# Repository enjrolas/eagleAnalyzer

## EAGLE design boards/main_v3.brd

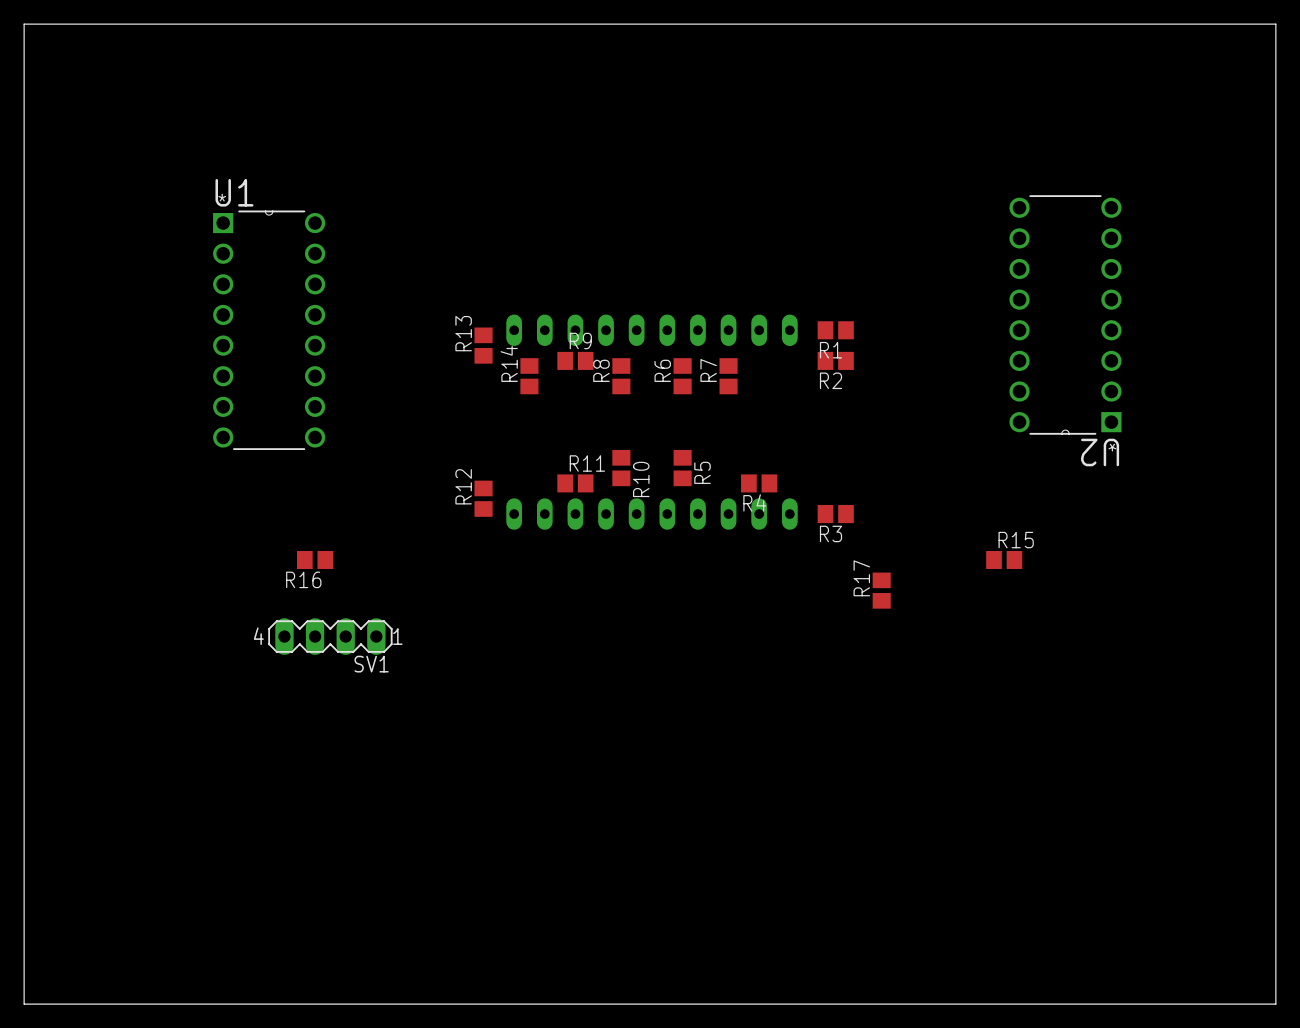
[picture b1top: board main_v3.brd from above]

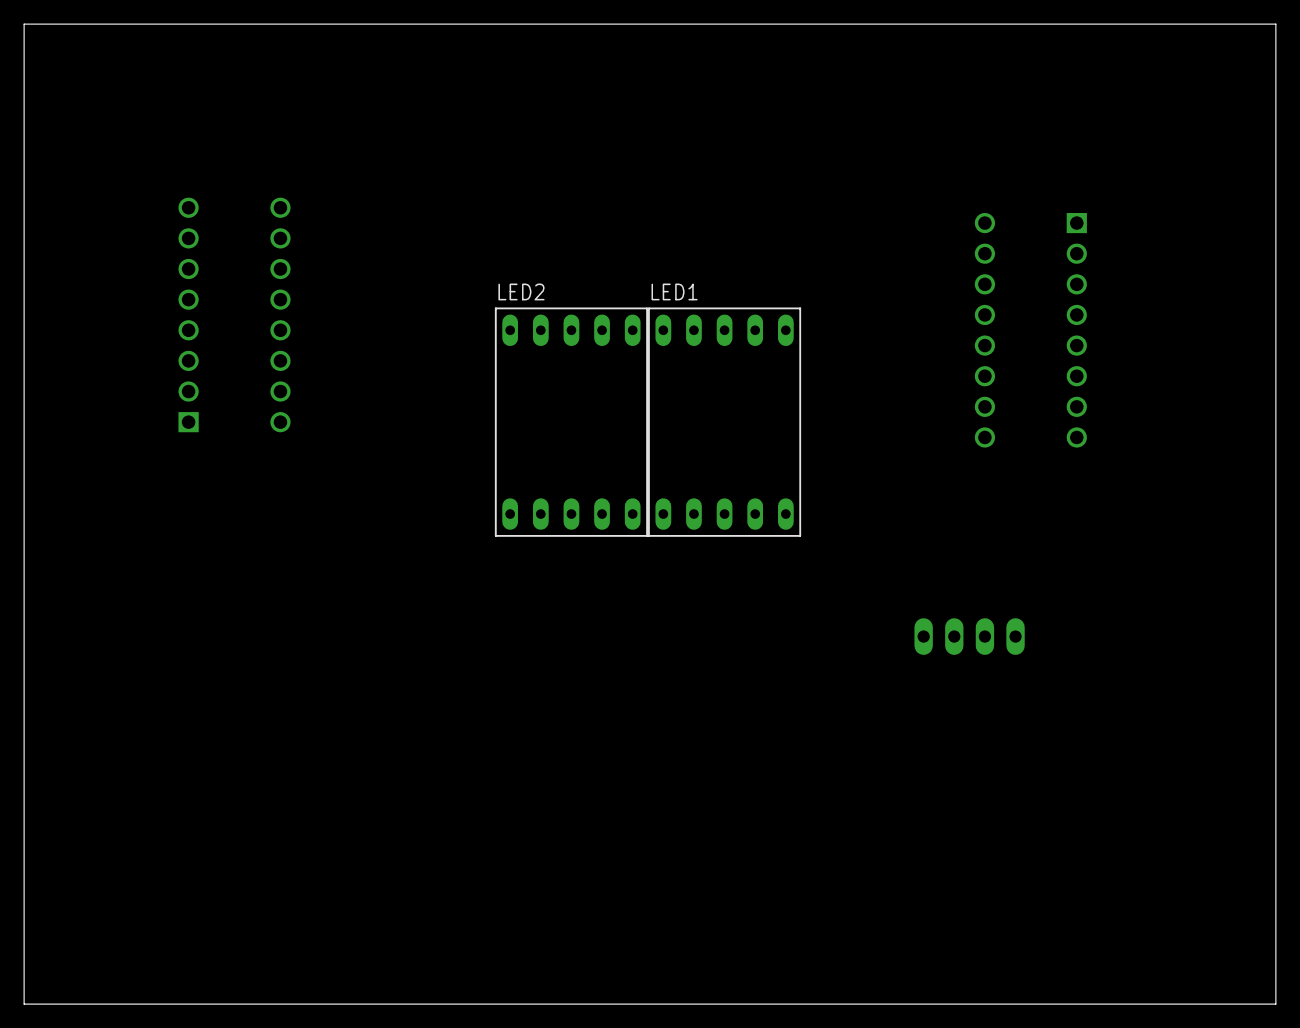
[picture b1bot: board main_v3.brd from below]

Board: 2 copper layers, 103.8 x 81.3 mm, 22 parts (2 on the bottom side), 33 nets, no tracks yet.

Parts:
LED1, LED2: 7-SEG_SA56-11; SA56-11
R1, R2, R3, R4, R5, R6, R7, R8, R9, R10, R11, R12, R13, R14: 220; R0805
R15, R16, R17: 10K; R0805
SV1: +5, 0, clock, reset; MA04-1
U1, U2: CD4026BE; DIP254P762X508-16

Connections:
+5V: SV1.1, U1.3, U1.16, U2.3, U2.16
GND: LED1.3, LED1.8, LED2.3, LED2.8, R15.1, R16.1, R17.1, SV1.2, U1.2, U1.8, U2.2, U2.8
unnamed: LED2.10, R1.2
unnamed: LED2.9, R2.2
unnamed: LED2.1, R3.2
unnamed: LED2.2, R4.2
unnamed: LED2.4, R5.2
unnamed: LED2.6, R6.2
unnamed: LED2.7, R7.2
unnamed: R7.1, U2.10
unnamed: R6.1, U2.12
unnamed: LED1.10, R8.2
unnamed: LED1.9, R9.2
unnamed: LED1.1, R10.2
unnamed: LED1.2, R11.2
unnamed: LED1.4, R12.2
unnamed: LED1.6, R13.2
unnamed: LED1.7, R14.2
unnamed: R5.1, U2.13
unnamed: R3.1, U2.11
unnamed: R2.1, U2.6
unnamed: R1.1, U2.7
unnamed: R14.1, U1.10
unnamed: R13.1, U1.12
unnamed: R12.1, U1.13
unnamed: R11.1, U1.9
unnamed: R10.1, U1.11
unnamed: R4.1, U2.9
unnamed: R9.1, U1.6
unnamed: R8.1, U1.7
unnamed: R16.2, SV1.3, U1.1
unnamed: R15.2, U1.5, U2.1
unnamed: R17.2, SV1.4, U1.15, U2.15

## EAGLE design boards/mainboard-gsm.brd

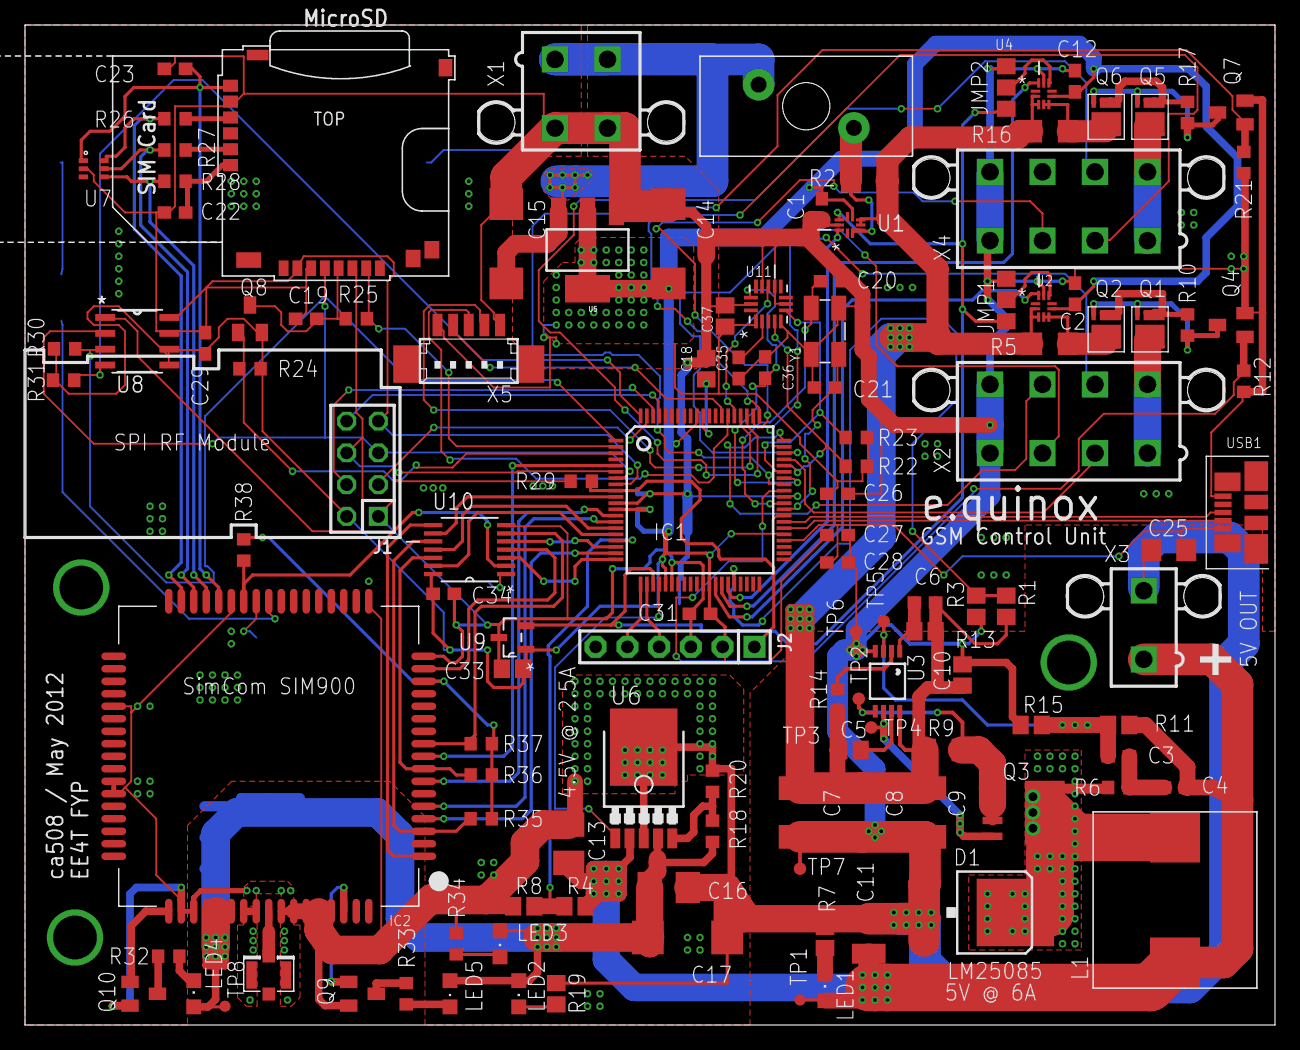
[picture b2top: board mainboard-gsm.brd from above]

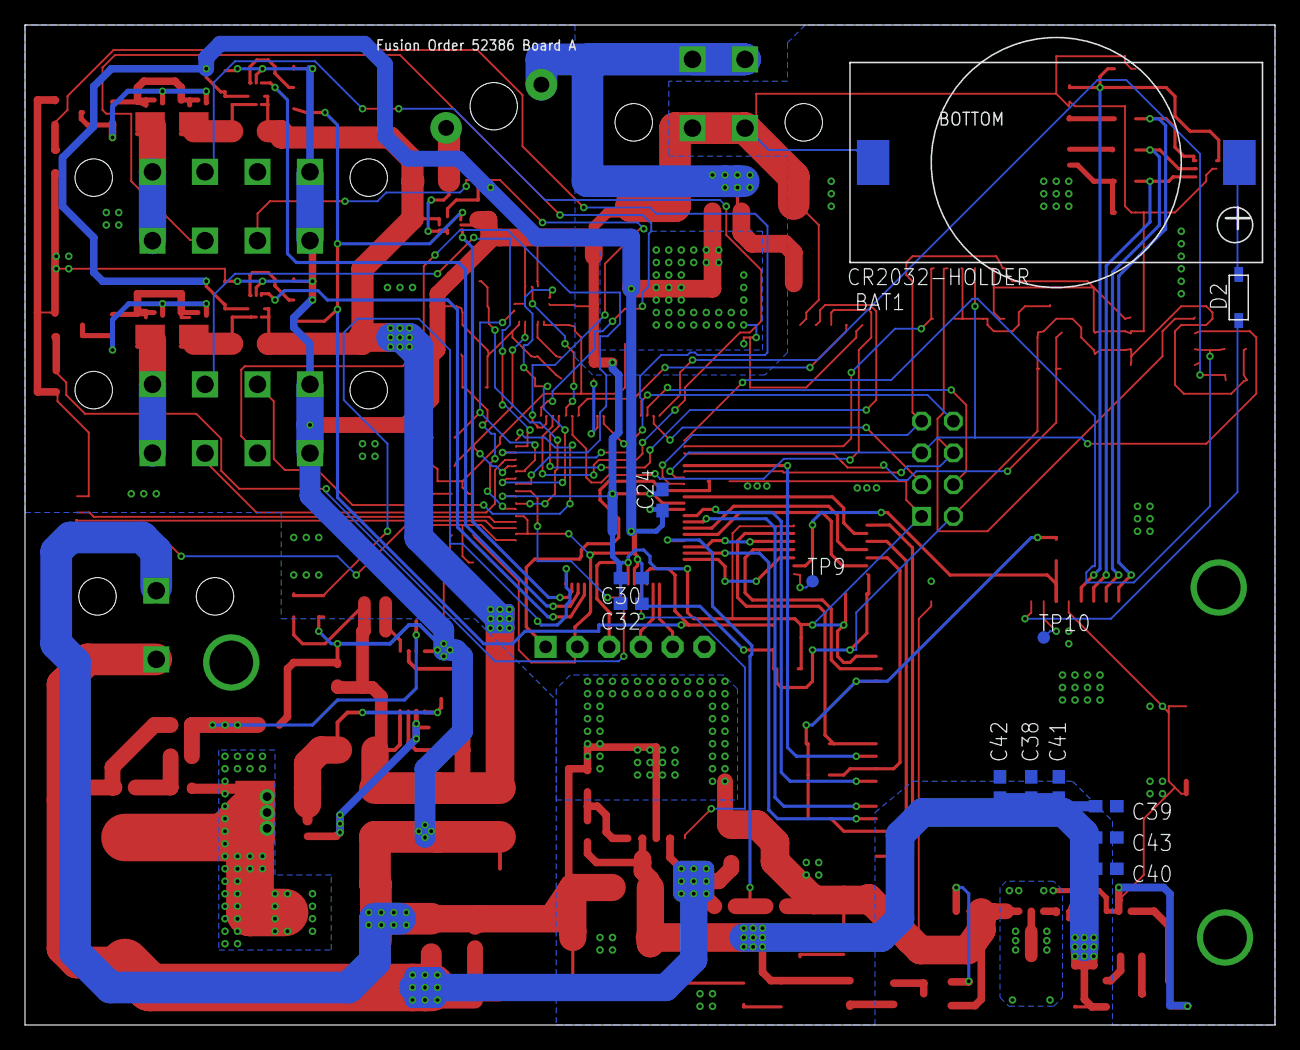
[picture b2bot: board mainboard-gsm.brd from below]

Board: 2 copper layers, 100.0 x 80.0 mm, 137 parts (13 on the bottom side), 107 nets.

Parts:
ANT1: U.FL
BAT1: CR2032-HOLDER; CH28-2032L
C1, C2, C3, C12: 0.1u; C0603
C4: 3300pF; C0603
C5: 0.47uF; C0805
C6: 1000pF; C0603
C7, C8, C9: 22u; C1812
C10: 1u; C0805
C11: 100u; C1210
C13, C16: 100u; B/3528-21R
C14, C15, C17: 10u; D/7343-31R
C18: 10uF; C0805
C19, C20, C21, C24, C26, C27, C28, C29, C30, C31, C32, C34, C35, C36, C43: 100nF; C0603
C22, C23: 22pF; C0603
C25: 0.47uF; C1206
C33: 0.47u; C0805
C37: 4.7uF; C0805
C38: 10nF; C0603
C39: 10pF; C0603
C40: 8.2pF; C0603
C41: 39pF; C0603
C42: 33pF; C0603
CONN1: MINIBLADE_SOCKET; LTF153008
D1: 6CWQ04FNPBF; TO252-AA
D2: SOD-123
IC1: PIC24FJ256GB108; TQFP80-12X12
IC2: SIM900_SMT
J1: F-2X04-DIL-100; DIL-100-2X04
J2: M-1X06-SIP-100-40; SIP-100-06-40
JMP1, JMP2: 0R-JUMPA; A0R-JMP
L1: 22uH; HC9-XXX-R
LED1, LED2, LED3, LED4, LED5: CHIPLED_0805
Q1, Q2, Q5, Q6: IRFHM9331PBF; IR_PQFN_FET
Q3: SI4401BDY; SO8-FET
Q4, Q7, Q10: SOT23
Q8: BSS84; SOT23
Q9: 2N2007; SOT23
R1: 30k; R0805
R2, R5, R16: 0.002; R1206
R3, R11: 10k; R0805
R4: 2k; R0805
R6: 68k; R0603
R7, R19: 2.7k; R0805
R8: 3k; R0805
R9: 10m; R1206
R10, R17, R30, R31: 100k; R0603
R12, R21, R24, R25, R29: 10k; R0603
R13: 2.37k; R0805
R14: 88.7k; R0603
R15: 3.4k; R0805
R18: 57k; R0603
R20: 22k; R0603
R22, R23: 2.7k; R0603
R26, R27, R28: 22; R0603
R32, R33, R34: 300; R0603
R35, R36, R37, R38: 2K7; R0603
SLOT1: MOLEX_SD_SIM_CONN; MOLEX_SDSIM_COMBO
TP1, TP8: TPTP09R; TP09R
TP2, TP3, TP4, TP5, TP6, TP7, TP9, TP10: TPTP10R; TP10R
U1, U2, U4: INA199A2RSWT; QFN40P140X180X55-10N
U3: LM25085MME; MINI-SO8
U5: SOT223
U6: MIC35302; TO252-5
U7: SC70-6L
U8: AT45DB081D-SSU; SOIC127P600X175-8N
U9: REF3012AIDBZT; SOT95P237X112-3N
U10: SN74LVC07APW; SOP65P640X120-14N
U11: MMA8453Q; QFN50P300X300X100-16N
USB1: MOLEX47346-0001; 47346-0001
X1: 5566-4
X2, X4: 5566-8
X3: 5566-2
X5: 53398-05
Y1: TXC-7B

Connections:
1.25VREF: IC1.23, JMP1.1, JMP2.1, U1.8, U9.2
2.8V: IC2.P$15, R35.2, R36.2, R37.2, R38.2
3.8V: C16.+, C17.+, C38.2, C39.2, C40.2, C41.2, C42.2, C43.2, IC2.P$55, IC2.P$56, IC2.P$57, LED2.A, LED3.A, LED4.A, LED5.A, R18.2, TP8.TP, U6.4
!FLASH_CS!: IC1.80, R31.2, U8.4
!FLASH_RESET!: IC1.1, R30.2, U8.3
!MCLR!: IC1.9, J2.1, R29.2
!RF_CS!: IC1.78, J1.4
!SD_CS!: IC1.2, R25.1, SLOT1.T2
!SD_ON!: IC1.3, Q8.1, R24.1
+3V3: C1.1, C2.1, C12.1, C14.+, C24.1, C26.2, C27.2, C29.1, C30.1, C31.1, C32.1, C33.1, C34.1, C37.1, IC1.12, IC1.25, IC1.32, IC1.45, IC1.48, IC1.71, J1.2, J2.2, Q8.2, R22.2, R23.2, R24.2, R30.1, R31.1, U1.6, U2.6, U4.6, U5.2, U5.4, U8.5, U8.6, U9.1, U10.14, U11.1, X5.1
+5V: C4.1, C11.1, C13.+, L1.2, LED1.A, R4.2, R11.2, TP1.TP, U6.2, X3.1
+12V: C5.1, C6.1, C7.1, C8.1, C9.1, C10.1, R1.2, R2.2, R5.1, R9.1, R13.1, R14.1, R16.1, TP3.TP, U1.4, U1.5, U2.2, U2.3, U3.8, U4.2, U4.3
AN12: IC1.33, U2.10
AN13: IC1.34, U4.10
AN14: IC1.35, U1.10
AN15: IC1.36, R1.1, R3.2
AXMTR_INT1: IC1.65, U11.11
AXMTR_ON: C36.1, IC1.54, U11.14
DBG_RXD: IC2.P$28, R38.1, U10.2
DBG_RXD_H: TP9.TP, U10.1
DBG_TXD: IC2.P$27, TP10.TP
EN_GSM_PSU: IC1.24, U6.1
GND: ANT1.P$1, ANT1.P$2, BAT1.N, C1.2, C2.2, C7.2, C8.2, C9.2, C10.2, C11.2, C12.2, C13.-, C14.-, C15.-, C16.-, C17.-, C18.1, C19.2, C20.1, C21.1, C22.2, C23.2, C24.2, C25.1, C26.1, C27.1, C28.1, C29.2, C30.2, C31.2, C32.2, C33.2, C34.2, C35.2, C36.2, C37.2, C38.1, C39.1, C40.1, C41.1, C42.1, C43.1, D1.1, D1.3, IC1.11, IC1.26, IC1.31, IC1.51, IC2.P$17, IC2.P$18, IC2.P$29, IC2.P$39, IC2.P$45, IC2.P$46, IC2.P$53, IC2.P$54, IC2.P$58, IC2.P$59, IC2.P$61, IC2.P$62, IC2.P$63, IC2.P$64, IC2.P$65, J1.1, J2.3, JMP1.3, JMP2.3, Q4.2, Q7.2, Q9.2, Q10.2, R3.1, R7.1, R8.1, R12.1, R15.1, R19.1, R20.1, R21.1, R29.1, R34.1, SLOT1.S4, SLOT1.T6, TP6.TP, TP7.TP, U1.9, U2.9, U3.4, U4.9, U5.1, U6.3, U6.TAB, U7.2, U8.7, U9.3, U10.7, U11.5, U11.7, U11.10, U11.12, U11.15, USB1.5, X1.3, X1.4, X2.4, X2.8, X3.2, X4.4, X4.8, X5.5, Y1.2, Y1.4
GSM_CTS: IC1.13, IC2.P$7
GSM_DCD: IC1.14, IC2.P$5
GSM_DTR: IC2.P$3, R35.1, U10.10
GSM_DTR_H: IC1.15, U10.11
GSM_RESET: IC2.P$16, U10.4
GSM_RESET_H: IC1.20, U10.3
GSM_RI: IC1.19, IC2.P$4
GSM_RTS: IC2.P$8, R36.1, U10.12
GSM_RTS_H: IC1.16, U10.13
GSM_RXD: IC2.P$10, R37.1, U10.6
GSM_RXD_H: IC1.18, U10.5
GSM_STATUS: IC2.P$66, Q9.1
GSM_STATUS_H: Q9.3, R33.1
GSM_TXD: IC1.5, IC2.P$9
MISO: IC1.8, J1.7, SLOT1.T7, U8.8
MOSI: IC1.6, J1.6, SLOT1.T3, U8.1
unnamed: C35.1, U11.2
unnamed: R26.1, SLOT1.S2
unnamed: R27.1, SLOT1.S3
unnamed: C22.1, R28.1, SLOT1.S6
unnamed: ANT1.P$3, IC2.P$60
unnamed: Q10.3, R32.1
unnamed: LED5.C, R33.2
unnamed: LED4.C, R32.2
unnamed: BAT1.P, D2.A
unnamed: Q3.4, TP4.TP, U3.6
unnamed: D1.4, L1.1, Q3.5, Q3.6, Q3.7, Q3.8, Q3.D1, Q3.D2, Q3.D3, R6.1
unnamed: Q5.1, Q5.2, Q5.3, Q5.3B, Q6.1, Q6.2, Q6.3, Q6.3B, R17.2
unnamed: C5.2, U3.7
unnamed: Q3.1, Q3.2, Q3.3, R9.2, TP2.TP, U3.5
unnamed: Q5.4, Q6.4, Q7.3, R17.1
unnamed: C6.2, R13.2, U3.1
unnamed: JMP1.2, U2.8
unnamed: Q5.5, Q5.6, Q5.7, Q5.8, Q5.9, X4.1, X4.5
unnamed: Q1.1, Q1.2, Q1.3, Q1.3B, Q2.1, Q2.2, Q2.3, Q2.3B, R10.2
unnamed: Q1.4, Q2.4, Q4.3, R10.1
unnamed: C3.1, C4.2, R6.2
unnamed: C3.2, R11.1, R15.2, TP5.TP, U3.3
unnamed: LED3.C, R34.2
unnamed: Q1.5, Q1.6, Q1.7, Q1.8, Q1.9, X2.1, X2.5
unnamed: R18.1, R20.2, U6.5
unnamed: CONN1.2, R2.1, U1.2, U1.3
unnamed: JMP2.2, U4.8
unnamed: LED1.C, R7.2
unnamed: LED2.C, R19.2
unnamed: C18.2, IC1.70
NETLIGHT: IC2.P$52, Q10.1
OSCI: C21.2, IC1.49, Y1.1
OSCO: C20.2, IC1.50, Y1.3
PGEC2: IC1.21, J2.5
PGED2: IC1.22, J2.4
PORT1_IO0: IC1.57, X2.2
PORT1_IO1: IC1.58, X2.3
PORT1_IO2: IC1.59, X2.6
PORT1_IO3: IC1.60, X2.7
PORT1_IOUT: Q2.5, Q2.6, Q2.7, Q2.8, Q2.9, R5.2, U2.4, U2.5
PORT1_ON: IC1.52, Q4.1, R12.2
PORT2_IO0: IC1.61, X4.2
PORT2_IO1: IC1.62, X4.3
PORT2_IO2: IC1.63, X4.6
PORT2_IOUT: Q6.5, Q6.6, Q6.7, Q6.8, Q6.9, R16.2, U4.4, U4.5
PORT2_ON: IC1.53, Q7.1, R21.2
PWRKEY: IC2.P$1, U10.8
PWRKEY_H: IC1.10, U10.9
RF_CE: IC1.79, J1.3
RF_IRQ: IC1.77, J1.8
RT: R14.2, U3.2
SCL1: IC1.56, R22.1, U11.4
SCLK: IC1.7, J1.5, SLOT1.T5, U8.2
SDA1: IC1.55, R23.1, U11.6
SD_VDD: C19.1, Q8.3, R25.2, SLOT1.T4
SENSE_5V: IC1.17, R4.1, R8.2
SIM_CLK: IC2.P$32, R27.2, U7.5
SIM_DATA: IC2.P$31, R28.2, U7.4
SIM_RST: IC2.P$33, R26.2, U7.6
SIM_VDD: C23.1, IC2.P$30, SLOT1.S1, U7.1
U2_RTS: IC1.64, X5.4
U2_RXD: IC1.67, X5.2
U2_TXD: IC1.66, X5.3
UD_N: IC1.46, USB1.2
UD_P: IC1.47, USB1.3
USB_VBUS: C25.2, C28.2, IC1.44, USB1.1
V+: C15.+, CONN1.1, U5.3, X1.1, X1.2
VRTC: D2.C, IC2.P$26

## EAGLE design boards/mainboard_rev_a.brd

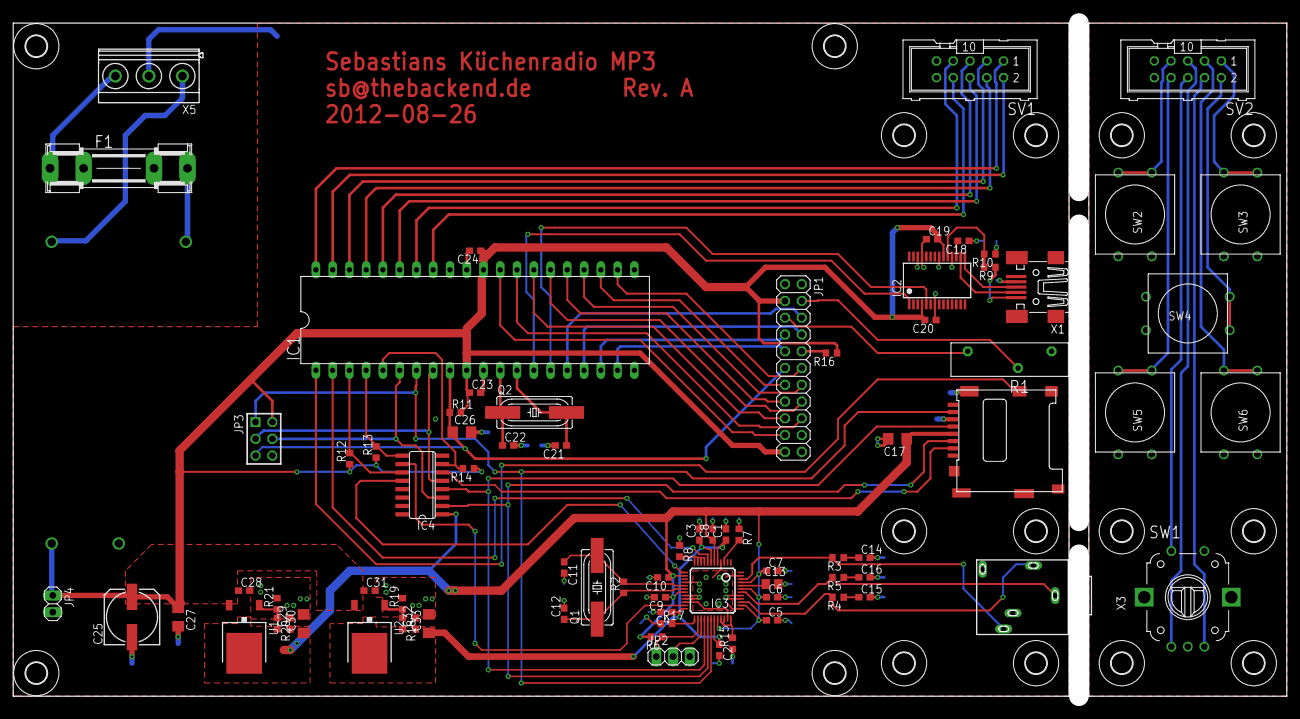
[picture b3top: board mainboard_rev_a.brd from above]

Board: 2 copper layers, 193.0 x 102.0 mm, 96 parts (1 on the bottom side), 78 nets.

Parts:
C1, C2, C3, C4, C5, C6, C7, C8, C9, C10, C18, C19, C20, C23, C24, C28, C29, C31, C32: 100n; C0603
C11, C12, C21, C22: 33p; C0603
C13: 1u; C0805
C14, C15: 10n; C0603
C16: 47n; C0603
C17, C27, C30, C33: C1206
C25: 153CLV-0807
C26: 10u; C1206
F1: FUSESHK20L; SHK20L
H1, H2, H3, H4, H5, H6, H7, H8, H9, H10, H11, H12, H13, H14, H15, H16: MOUNT-HOLE3.2; 3,2
IC1: MEGA164P/324P/644P-PU; DIL40
IC2: FT232RL; SSOP28
IC3: VS1053; LQFP-48
IC4: 4050D; SO16
JP1: 2X11
JP2: 1X03
JP3: AVR-ISP-6VERT; AVR-ISP-6
JP4: 1X02
Q1, Q2: HC49UP
R1: PT-SPIN
R2: R0603
R3, R4: 20; R0603
R5: 10; R0603
R6, R7, R8, R10, R11, R12, R13, R14, R15, R16, R17: 10k; R0603
R9, R18, R21: 4k7; R0603
R19: 2k2; R0603
R20: 2k8; R0603
SV1, SV2: ML10
SW1: ENCODER_SW1-PEC12; PEC12_INCREMENTAL_ENCODER
SW2, SW3, SW4, SW5, SW6: PUSHBUTTON_12X12
U1, U2: TS1117DT; TO252
X1: MINI-USB-32005-301; 32005-301
X2: MICRO-SD
X3: 1503_09
X4: TRACO_TMP_07105; TRACO_TMP_07
X5: MKDSN1,5/3-5,08

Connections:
!CE: IC1.17, JP1.8
!HALT: JP1.10, R16.2
!RD: IC1.18, JP1.7
!RESET: C26.1, IC1.9, JP1.11, JP3.5, R11.1
!WR: IC1.16, JP1.6
+1V8: C1.1, C2.1, C3.1, C4.1, C32.1, C33.1, IC3.5, IC3.7, IC3.24, IC3.31, R18.2, U2.3
+3V3: C5.1, C6.1, C7.1, C8.1, C9.1, C10.1, C17.1, C29.1, C30.1, IC3.6, IC3.14, IC3.19, IC3.32, IC3.38, IC3.43, IC3.45, IC4.1, R6.2, R20.2, U1.3, X2.4
+5V: C19.2, C20.2, C23.1, C24.1, C25.+, C27.1, C28.1, C31.1, IC1.10, IC1.30, IC2.4, IC2.20, JP1.3, JP1.21, JP3.2, JP4.1, R11.2, R12.1, R13.1, R14.1, R16.1, U1.2, U2.2, X4.3
C/!D: IC1.19, JP1.9
CS_!DCS!_I: IC1.3, IC4.11, R12.2
CS_INS: IC1.1, X2.K1
DB0: IC1.22, JP1.12
DB1: IC1.23, JP1.13
DB2: IC1.24, JP1.14
DB3: IC1.25, JP1.15
DB4: IC1.26, JP1.16
DB5: IC1.27, JP1.17
DB6: IC1.28, JP1.18
DB7: IC1.29, JP1.19
FTDI_RXD_IN: IC1.15, IC2.5
FTDI_TXD_OUT: IC1.14, IC2.1
GBUF: IC3.42, R5.2, X3.1
GND: C1.2, C2.2, C3.2, C4.2, C5.2, C6.2, C7.2, C8.2, C9.2, C10.2, C11.2, C12.2, C13.2, C14.2, C15.2, C16.2, C17.2, C18.1, C19.1, C20.1, C21.2, C22.2, C23.2, C24.2, C25.-, C26.2, C27.2, C28.2, C29.2, C30.2, C31.2, C32.2, C33.2, IC1.11, IC1.31, IC2.7, IC2.18, IC2.21, IC2.25, IC2.26, IC3.4, IC3.16, IC3.20, IC3.21, IC3.22, IC3.35, IC3.37, IC3.40, IC3.41, IC3.47, IC4.8, JP1.1, JP1.2, JP1.22, JP2.3, JP3.6, JP4.2, R1.1, R7.1, R8.1, R10.1, R15.1, R17.1, R19.2, R21.2, SV1.9, SV1.10, SV2.9, SV2.10, SW1.C, SW1.P2, SW2.A@1, SW2.A@2, SW3.A@1, SW3.A@2, SW4.A@1, SW4.A@2, SW5.A@1, SW5.A@2, SW6.A@1, SW6.A@2, X1.4, X2.6, X2.K2, X4.4, X5.2
LCD_VEE: JP1.5, R1.2
LEFT: IC3.46, R3.2, X3.3
MISO: IC1.7, IC3.30, JP3.1, X2.7
MOSI: IC1.6, IC4.3, JP3.4
MOSI_3V: IC3.29, IC4.2, X2.3
unnamed: JP1.4, R1.3
unnamed: C13.1, IC3.44
unnamed: IC3.9, IC3.10, IC3.11, IC3.12, R8.2
unnamed: IC3.33, IC3.34, IC3.36, R15.2
unnamed: F1.1A, X5.3
unnamed: C14.1, R3.1
unnamed: C15.1, R4.1
unnamed: C11.1, IC3.17, Q1.2, R2.2
unnamed: C16.1, R5.1
unnamed: C12.1, IC3.18, Q1.1, R2.1
unnamed: IC3.3, R7.2
unnamed: F1.2A, X4.2
unnamed: C18.2, IC2.17
unnamed: IC2.16, X1.2
unnamed: IC2.15, X1.3
unnamed: R9.1, X1.1
unnamed: IC2.19, R9.2, R10.2
unnamed: C21.1, IC1.13, Q2.2
unnamed: C22.1, IC1.12, Q2.1
unnamed: X4.1, X5.1
unnamed: IC3.25, R17.2
unnamed: R20.1, R21.1, U1.1
unnamed: R18.1, R19.1, U2.1
RIGHT: IC3.39, R4.2, X3.2
SCK: IC1.8, IC4.5, JP3.3
SCK_3V: IC3.28, IC4.4, X2.5
SD_!CS: IC4.6, X2.2
SD_!CS!_I: IC1.5, IC4.7, R14.2
SW_0: IC1.40, SV1.1
SW_1: IC1.39, SV1.2
SW_2: IC1.38, SV1.3
SW_3: IC1.37, SV1.4
SW_4: IC1.36, SV1.5
SW_5: IC1.35, SV1.6
SW_6: IC1.34, SV1.7
SW_7: IC1.33, SV1.8
SW_A: SV2.7, SW2.B@1, SW2.B@2
SW_B: SV2.1, SW3.B@1, SW3.B@2
SW_C: SV2.2, SW4.B@1, SW4.B@2
SW_D: SV2.8, SW5.B@1, SW5.B@2
SW_E: SV2.3, SW6.B@1, SW6.B@2
SW_F: SV2.5, SW1.A
SW_G: SV2.4, SW1.B
SW_H: SV2.6, SW1.P1
VS_!CS: IC3.23, IC4.10
VS_!CS!_I: IC1.4, IC4.9, R13.2
VS_!DCS: IC3.13, IC4.12
VS_!DREQ: IC1.2, IC3.8
VS_RXD: IC3.26, JP2.1, R6.1
VS_TXD: IC3.27, JP2.2

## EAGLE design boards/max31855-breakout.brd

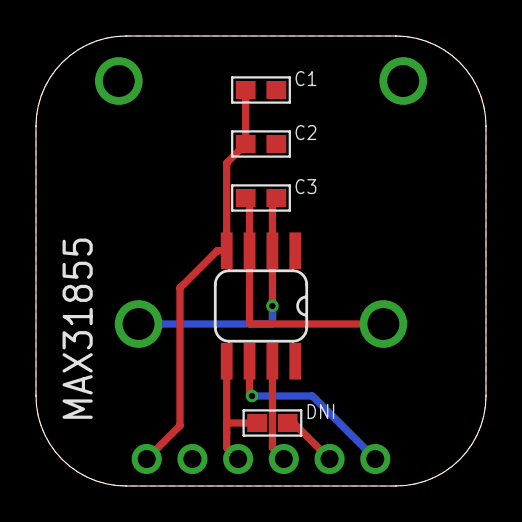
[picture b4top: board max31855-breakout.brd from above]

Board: 2 copper layers, 25.0 x 25.0 mm, 7 parts (1 on the bottom side), 8 nets.

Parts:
C1: .1uF; 0603
C2: 1uF; 0603
C3: 10nF; 0603
DNI: DNI; 0603
JP1: 1X06_ROUND
U$1: MAX31855; SO-08
U$2: OMEGAPCC-SMP; PCC-SMP

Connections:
3V3: C1.1, C2.1, JP1.1, U$1.4
CS: JP1.6, U$1.6
GND: C1.2, C2.2, JP1.2, U$1.1, U$2.GND@1, U$2.GND@4
SCK: DNI.1, JP1.3, U$1.5
SI: DNI.2, JP1.5
SO: JP1.4, U$1.7
T+: C3.1, U$1.3, U$2.+2
T-: C3.2, U$1.2, U$2.-3

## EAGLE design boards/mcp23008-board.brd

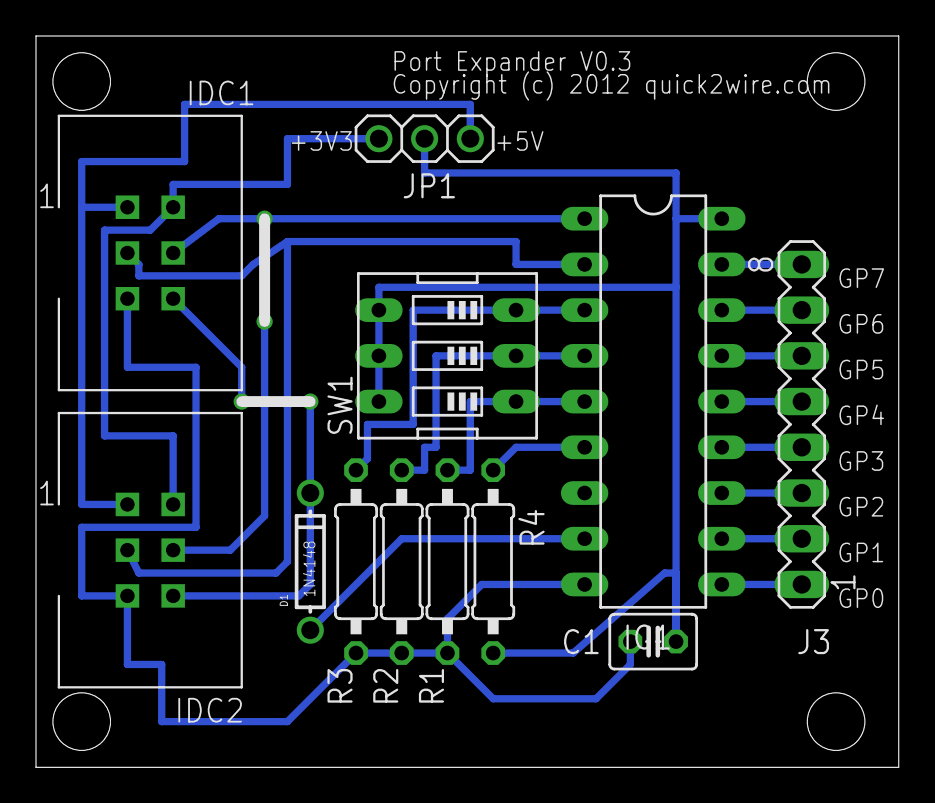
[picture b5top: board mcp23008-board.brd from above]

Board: 2 copper layers, 47.9 x 40.6 mm, 12 parts (0 on the bottom side), 20 nets.

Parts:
C1: 0u1; C025-030X050
D1: 1N4148; DO-1N4148
IC1: MCP23008; DIL18
IDC1, IDC2: IDC-6W
J3: MA08-1
JP1: 1X03
R1, R2, R3, R4: 4K7; 0207/10
SW1: EDG-03

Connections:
A0: IC1.5, R1.2, SW1.1
A1: IC1.4, R2.2, SW1.2
A2: IC1.3, R3.2, SW1.3
GND: C1.2, IC1.9, IDC1.P$5, IDC2.P$5, R1.1, R2.1, R3.1
GP0: IC1.10, J3.1
GP1: IC1.11, J3.2
GP2: IC1.12, J3.3
GP3: IC1.13, J3.4
GP4: IC1.14, J3.5
GP5: IC1.15, J3.6
GP6: IC1.16, J3.7
GP7: IC1.17, J3.8
INT: D1.A, IC1.8
unnamed: IC1.2, IDC1.P$3, IDC2.P$3
unnamed: IC1.1, IDC1.P$4, IDC2.P$4
unnamed: D1.C, IDC1.P$6, IDC2.P$6
unnamed: IDC1.P$2, IDC2.P$2, JP1.1
unnamed: C1.1, IC1.18, JP1.2, R4.2, SW1.4, SW1.5, SW1.6
unnamed: IC1.6, R4.1
VCC: IDC1.P$1, IDC2.P$1, JP1.3

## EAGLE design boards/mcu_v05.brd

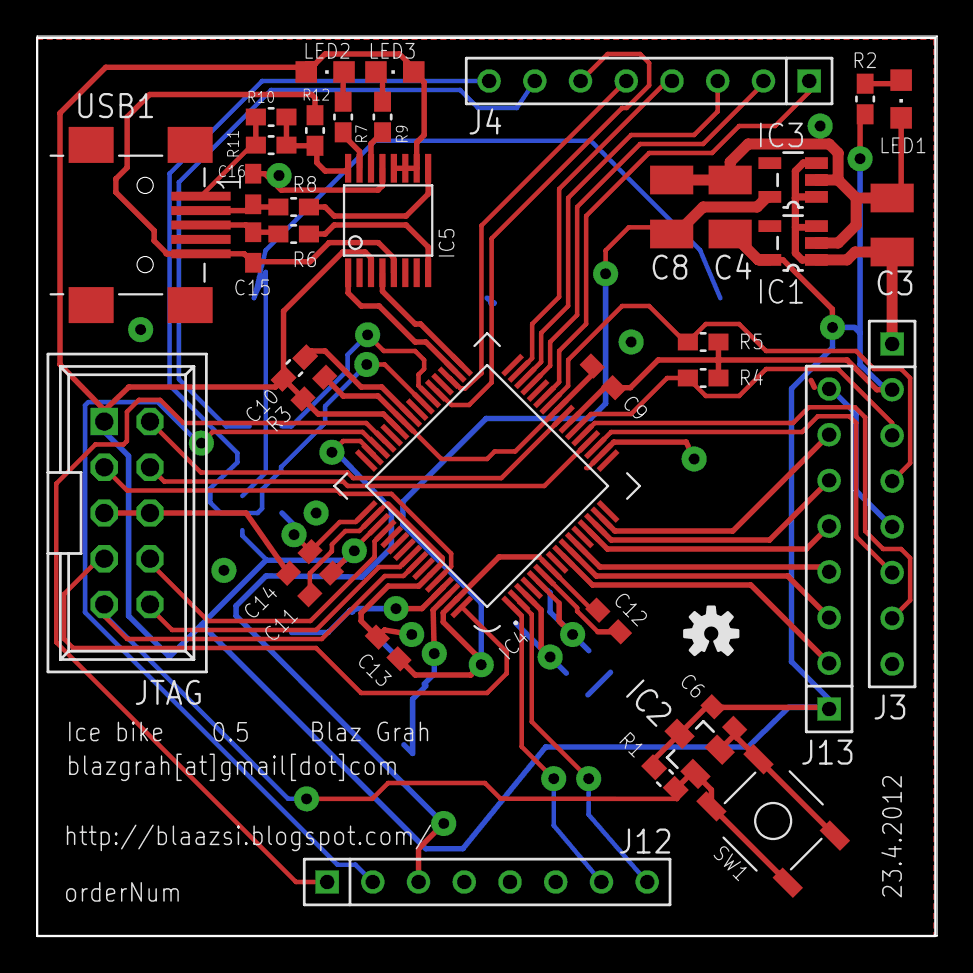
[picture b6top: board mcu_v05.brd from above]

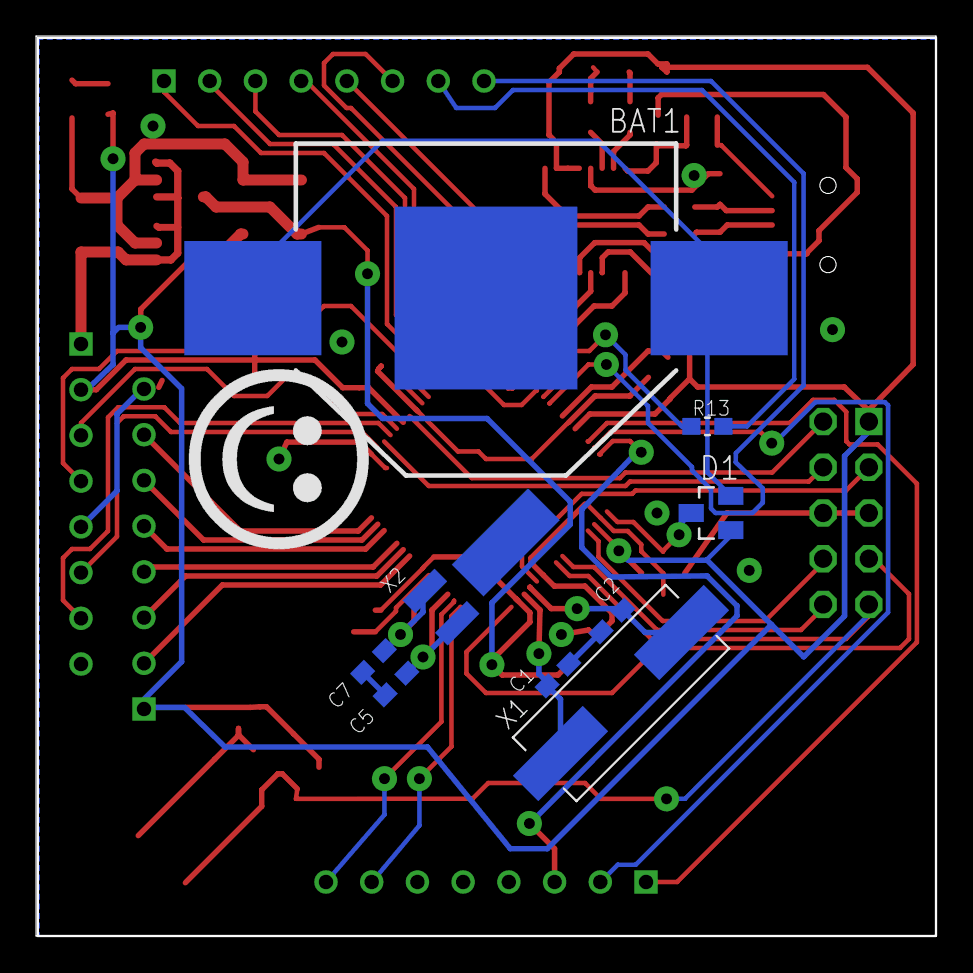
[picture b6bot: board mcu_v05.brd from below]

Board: 2 copper layers, 50.0 x 50.0 mm, 52 parts (9 on the bottom side), 55 nets.

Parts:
BAT1: CR2032; BATTERY_20MM_SMD
C1, C2: 39p; C0603
C3: 22u/10V; SMC_B
C4, C8: 47u/6.3V; SMC_B
C5, C7: 22p; C0603
C6, C9, C10, C11, C12, C13, C14: 100n; C0603
C15, C16: 47p; C0603
D1: BAT54C; SOT23
DOC: FRAME_DINA4_L; DP_LOGO
IC1, IC3: SP6205_3V3_VREG; SOT23-5
IC2: MCP111T_300; SOT23
IC4: LPC2138; LQFP64
IC5: FT230XS_FTDI; SSOP16
J3, J4, J12, J13: CON_HEADER_1X08-PTH; M1X8
JTAG: CON_HEADER_2X05-PTH+SHROUDED_A; PINSHRD_PTH_2X05
LED1: RED; LED0805
LED2, LED3: GREEN; LED0805
LOGO1: OSHW-LOGOS; OSHW-LOGO-S
PCB1: PCB; PCB_50X50
R1, R3, R10, R11, R12: 10K; R0603
R2, R7, R9: 330; R0603
R4, R5: 4K7; R0603
R6, R8: 27; R0603
R13: 0R; R0603_JUMP
SW1: RST; BUTTON_SW_4P_SMD
U$13: LOGO; LOGO_SMILE
USB1: CON-USB-F-MINI-B; CONN_USB_MINI-B
X1: 12M; CRYSTAL_12M_4.8X10.6MM
X2: 32K; CRYSTAL_32K_SMD

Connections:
3V3: C4.+, C6.1, C9.1, C10.1, C11.1, D1.1, IC1.5, IC2.3, IC4.23, IC4.43, IC4.51, IC5.P$3, IC5.P$10, IC5.P$11, IC5.P$12, J3.2, J13.1, JTAG.1, LED2.A, LED3.A, R1.2, R2.2, R3.2, R4.2, R5.2
5V: C3.+, IC1.1, IC1.3, IC3.1, IC3.3, J3.1
BSL: IC4.41, R3.1
GND: BAT1.NEG, C1.1, C2.1, C3.-, C4.-, C5.1, C6.2, C7.1, C8.-, C9.2, C10.2, C11.2, C12.2, C13.2, C14.2, C15.2, C16.2, IC1.2, IC2.2, IC3.2, IC4.6, IC4.18, IC4.25, IC4.42, IC4.50, IC4.59, IC5.P$5, IC5.P$13, J3.5, J3.8, J12.4, J12.5, J12.6, J13.8, JTAG.5, JTAG.6, LED1.C, R12.1, SW1.1, SW1.2, USB1.GND
unnamed: LED1.A, R2.1
unnamed: BAT1.POS1, BAT1.POS2, D1.2
unnamed: C16.1, R8.1, USB1.D-
unnamed: C15.1, R6.1, USB1.D+
unnamed: IC5.P$9, R8.2
unnamed: IC5.P$8, R6.2
unnamed: R10.2, R11.2, USB1.VUSB
unnamed: IC5.P$16, R10.1, R11.1, R12.2
unnamed: IC5.P$14, R9.1
unnamed: LED2.C, R7.2
unnamed: LED3.C, R9.2
unnamed: IC5.P$15, R7.1
P0.4: IC4.27, J4.1
P0.5: IC4.29, J4.2
P0.6: IC4.30, J4.3
P0.7: IC4.31, J4.4
P0.10: IC4.35, J4.5
P0.11: IC4.37, J4.6
P0.12: IC4.38, R13.1
P0.12A: J4.7, R13.2
P0.13: IC4.39, J4.8
P0.15: IC4.45, J12.1
P0.16: IC4.46, J12.2
P0.17: IC4.47, J12.3
P0.21: IC4.1, J12.7
P0.22: IC4.2, J12.8
P0.25: IC4.9, J13.2
P0.26: IC4.10, J13.3
P0.27: IC4.11, J13.4
P0.28: IC4.13, J13.5
P0.29: IC4.14, J13.6
P0.30: IC4.15, J13.7
RST: IC2.1, IC4.57, JTAG.9, R1.1, SW1.3, SW1.4
RTCK: IC4.24, JTAG.2
RTXC1: C5.2, IC4.3, X2.X2
RTXC2: C7.2, IC4.5, X2.X1
RXD0: IC4.21, J3.7
RXD1: IC4.34, IC5.P$1
SCL0: IC4.22, J3.3, R4.1
SDA0: IC4.26, J3.4, R5.1
TCK: IC4.56, JTAG.10
TDI: IC4.60, JTAG.3
TDO: IC4.64, JTAG.7
TMS: IC4.52, JTAG.8
TRST: IC4.20, JTAG.4
TXD0: IC4.19, J3.6
TXD1: IC4.33, IC5.P$4
VBAT: C14.1, D1.3, IC4.49
VDDA: C8.+, C12.1, C13.1, IC3.5, IC4.7, IC4.63
XTAL1: C1.2, IC4.62, X1.P$2
XTAL2: C2.2, IC4.61, X1.P$1

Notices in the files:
boards/mcp23008-board.brd:
Copyright (c) 2012 quick2wire.com
boards/mcu_v05.brd:
LICENSE: OSHW
parts and their libraries:
SparkFun-Connectors: Licensing: CC v3.0 Share-Alike You are welcome to use this library for commercial purposes.
con-headers-jp: Copyright (C) 2008, Bob Starr
